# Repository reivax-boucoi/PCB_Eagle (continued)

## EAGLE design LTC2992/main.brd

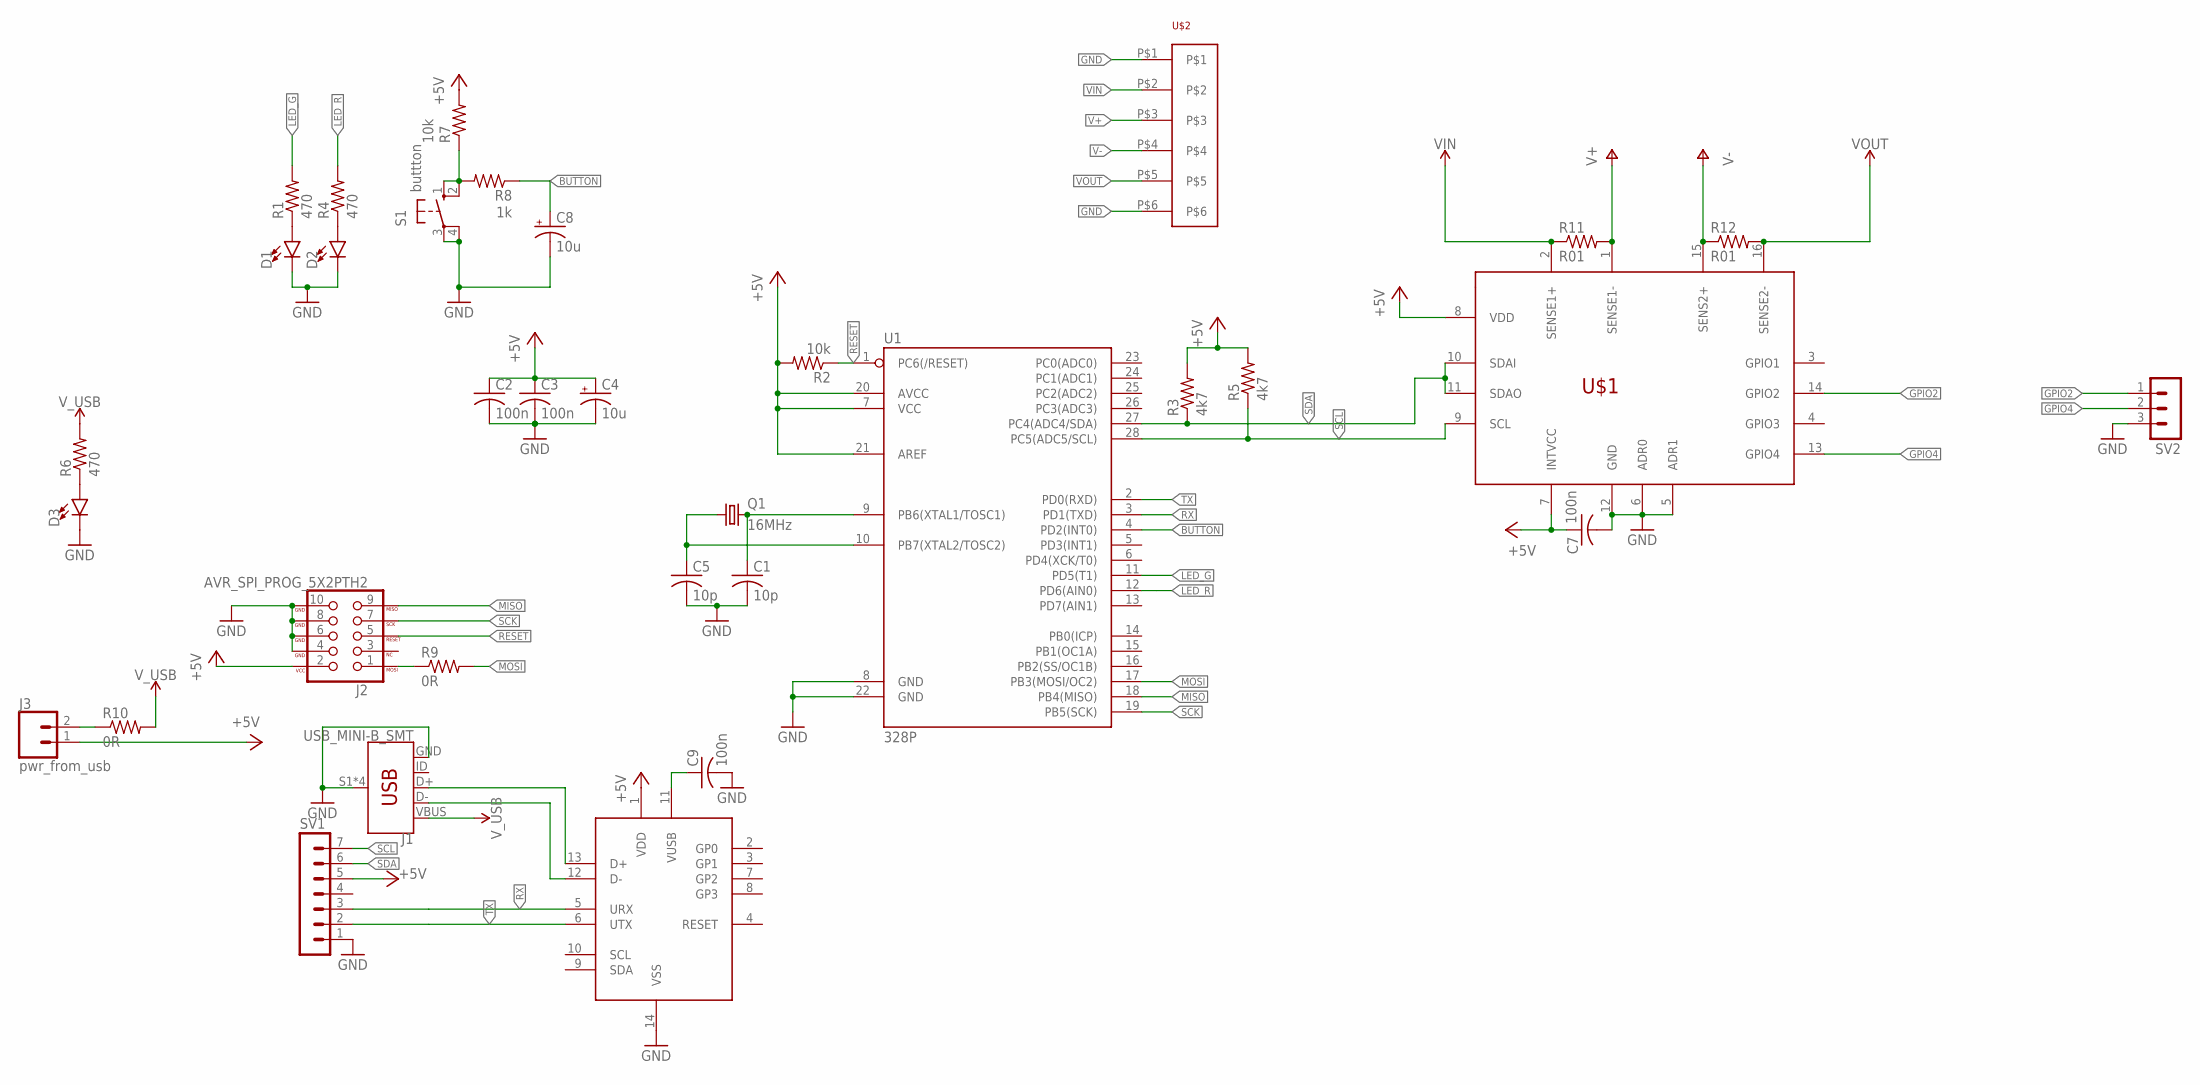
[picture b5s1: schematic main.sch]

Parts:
BR1: MCP2221A; DIP14
C1, C5: 10p; C0603
C2, C9: 100n; C050-030X075
C3, C7: 100n; C0805
C4: 10u; E2,5-6E
C8: 10u; E5-5
D1, D2, D3: LED3MM; LED_3MM
J1: USB_MINI-B_SMT; USB-MINIB
J2: AVR_SPI_PROG_5X2PTH2; 2X5-SHROUDED
J3: pwr_from_usb; 1X02
Q1: 16MHz; HC49U70
R1, R4, R6: 470; R0805
R2: 10k; 0204/7
R3, R5: 4k7; 0207/10
R7: 10k; R0805
R8: 1k; R0805
R9: 0R; 0204/7
R10: 0R; 0207/15
R11, R12: R01; R2512
S1: buttton; B3F-10XX
SV1: MA07-1
SV2: MA03-1
U1: 328P; DIP28
U$1: LTC2992; MSOP16
U$2: SCREWTERM_5MM_6WAY

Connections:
+5V: BR1.1 (VDD), C2.1, C3.1, C4.+, C7.1, J2.2 (VCC), J3.1, R2.2, R3.2, R5.2, R7.2, SV1.5, U1.7 (VCC), U1.20 (AVCC), U1.21 (AREF), U$1.7 (INTVCC), U$1.8 (VDD)
BUTTON: C8.+, R8.1, U1.4 (PD2(INT0))
GND: BR1.14 (VSS), C1.2, C2.2, C3.2, C4.-, C5.2, C7.2, C8.-, C9.2, D1.K (C), D2.K (C), D3.K (C), J1.GND, J1.S1 (SHIELD), J1.S2 (SHIELD), J1.S3 (SHIELD), J1.S4 (SHIELD), J2.4 (GND), J2.6 (GND), J2.8 (GND), J2.10 (GND), S1.3, S1.4 (P1), SV1.1, SV2.3, U1.8 (GND), U1.22 (GND), U$1.5 (ADR1), U$1.6 (ADR0), U$1.12 (GND), U$2.P$1, U$2.P$6
GPIO2: SV2.1, U$1.14 (GPIO2)
GPIO4: SV2.2, U$1.13 (GPIO4)
LED_G: R1.2, U1.11 (PD5(T1))
LED_R: R4.2, U1.12 (PD6(AIN0))
MISO: J2.9 (MISO), U1.18 (PB4(MISO))
MOSI: R9.2, U1.17 (PB3(MOSI/OC2))
unnamed: C1.1, Q1.2, U1.9 (PB6(XTAL1/TOSC1))
unnamed: C5.1, Q1.1, U1.10 (PB7(XTAL2/TOSC2))
unnamed: D3.A, R6.1
unnamed: BR1.13 (D+), J1.D+
unnamed: BR1.12 (D-), J1.D-
unnamed: D2.A, R4.1
unnamed: R7.1, R8.2, S1.1 (S), S1.2 (S1)
unnamed: D1.A, R1.1
unnamed: J2.1 (MOSI), R9.1
unnamed: BR1.11 (VUSB), C9.1
unnamed: J3.2, R10.1
RESET: J2.5 (RESET), R2.1, U1.1 (PC6(/RESET))
RX: BR1.5 (URX), SV1.3, U1.3 (PD1(TXD))
SCK: J2.7 (SCK), U1.19 (PB5(SCK))
SCL: R5.1, SV1.7, U1.28 (PC5(ADC5/SCL)), U$1.9 (SCL)
SDA: R3.1, SV1.6, U1.27 (PC4(ADC4/SDA)), U$1.10 (SDAI), U$1.11 (SDAO)
TX: BR1.6 (UTX), SV1.2, U1.2 (PD0(RXD))
V+: R11.2, U$1.1 (SENSE1-), U$2.P$3
V-: R12.1, U$1.15 (SENS2+), U$2.P$4
VIN: R11.1, U$1.2 (SENSE1+), U$2.P$2
VOUT: R12.2, U$1.16 (SENSE2-), U$2.P$5
V_USB: J1.VBUS, R6.2, R10.2

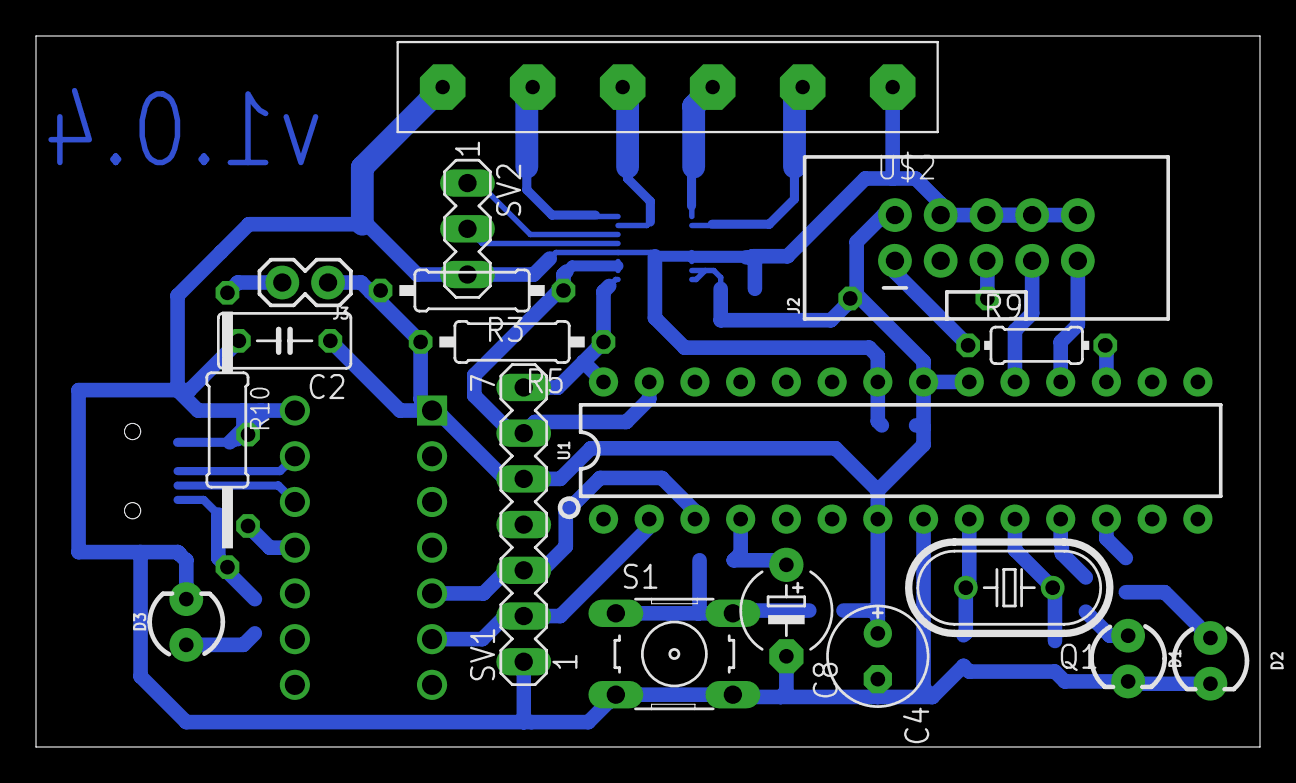
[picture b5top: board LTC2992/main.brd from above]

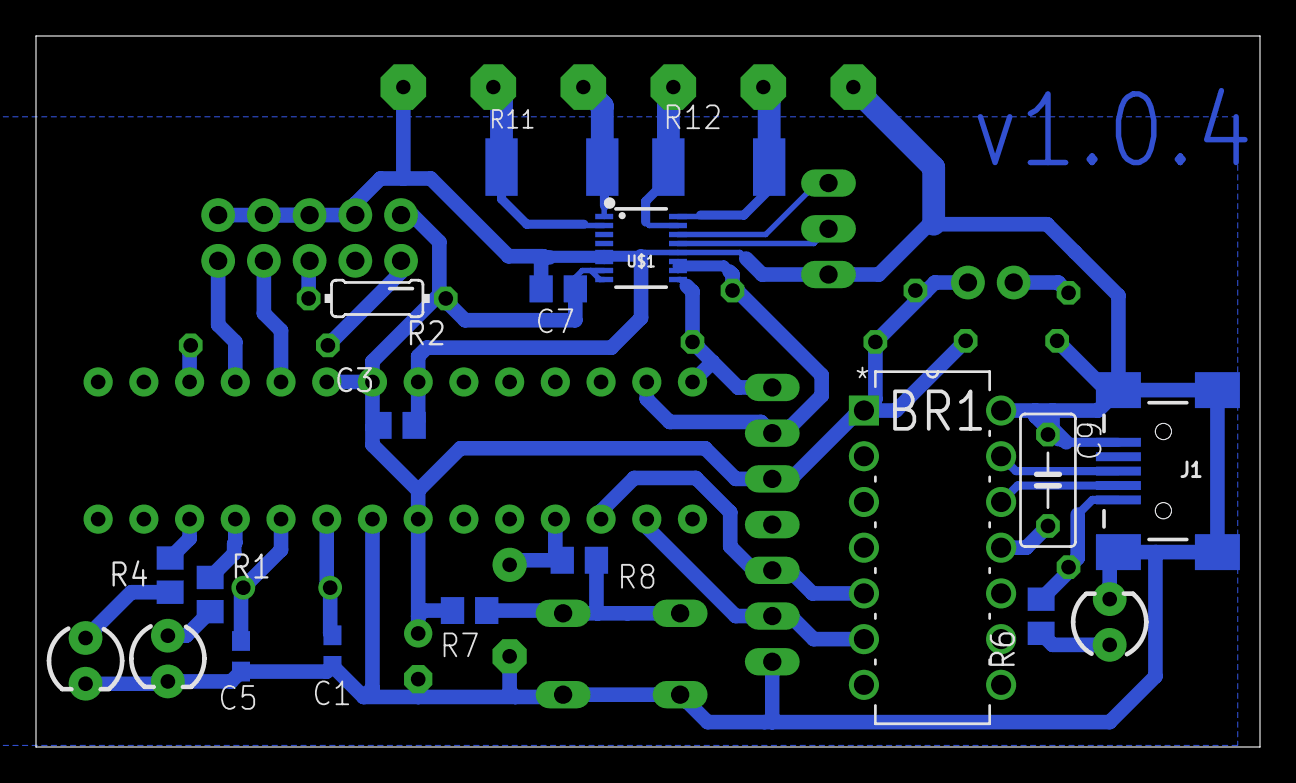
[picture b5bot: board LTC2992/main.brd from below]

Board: 2 copper layers, 68.0 x 39.5 mm, 34 parts (16 on the bottom side), 31 nets.

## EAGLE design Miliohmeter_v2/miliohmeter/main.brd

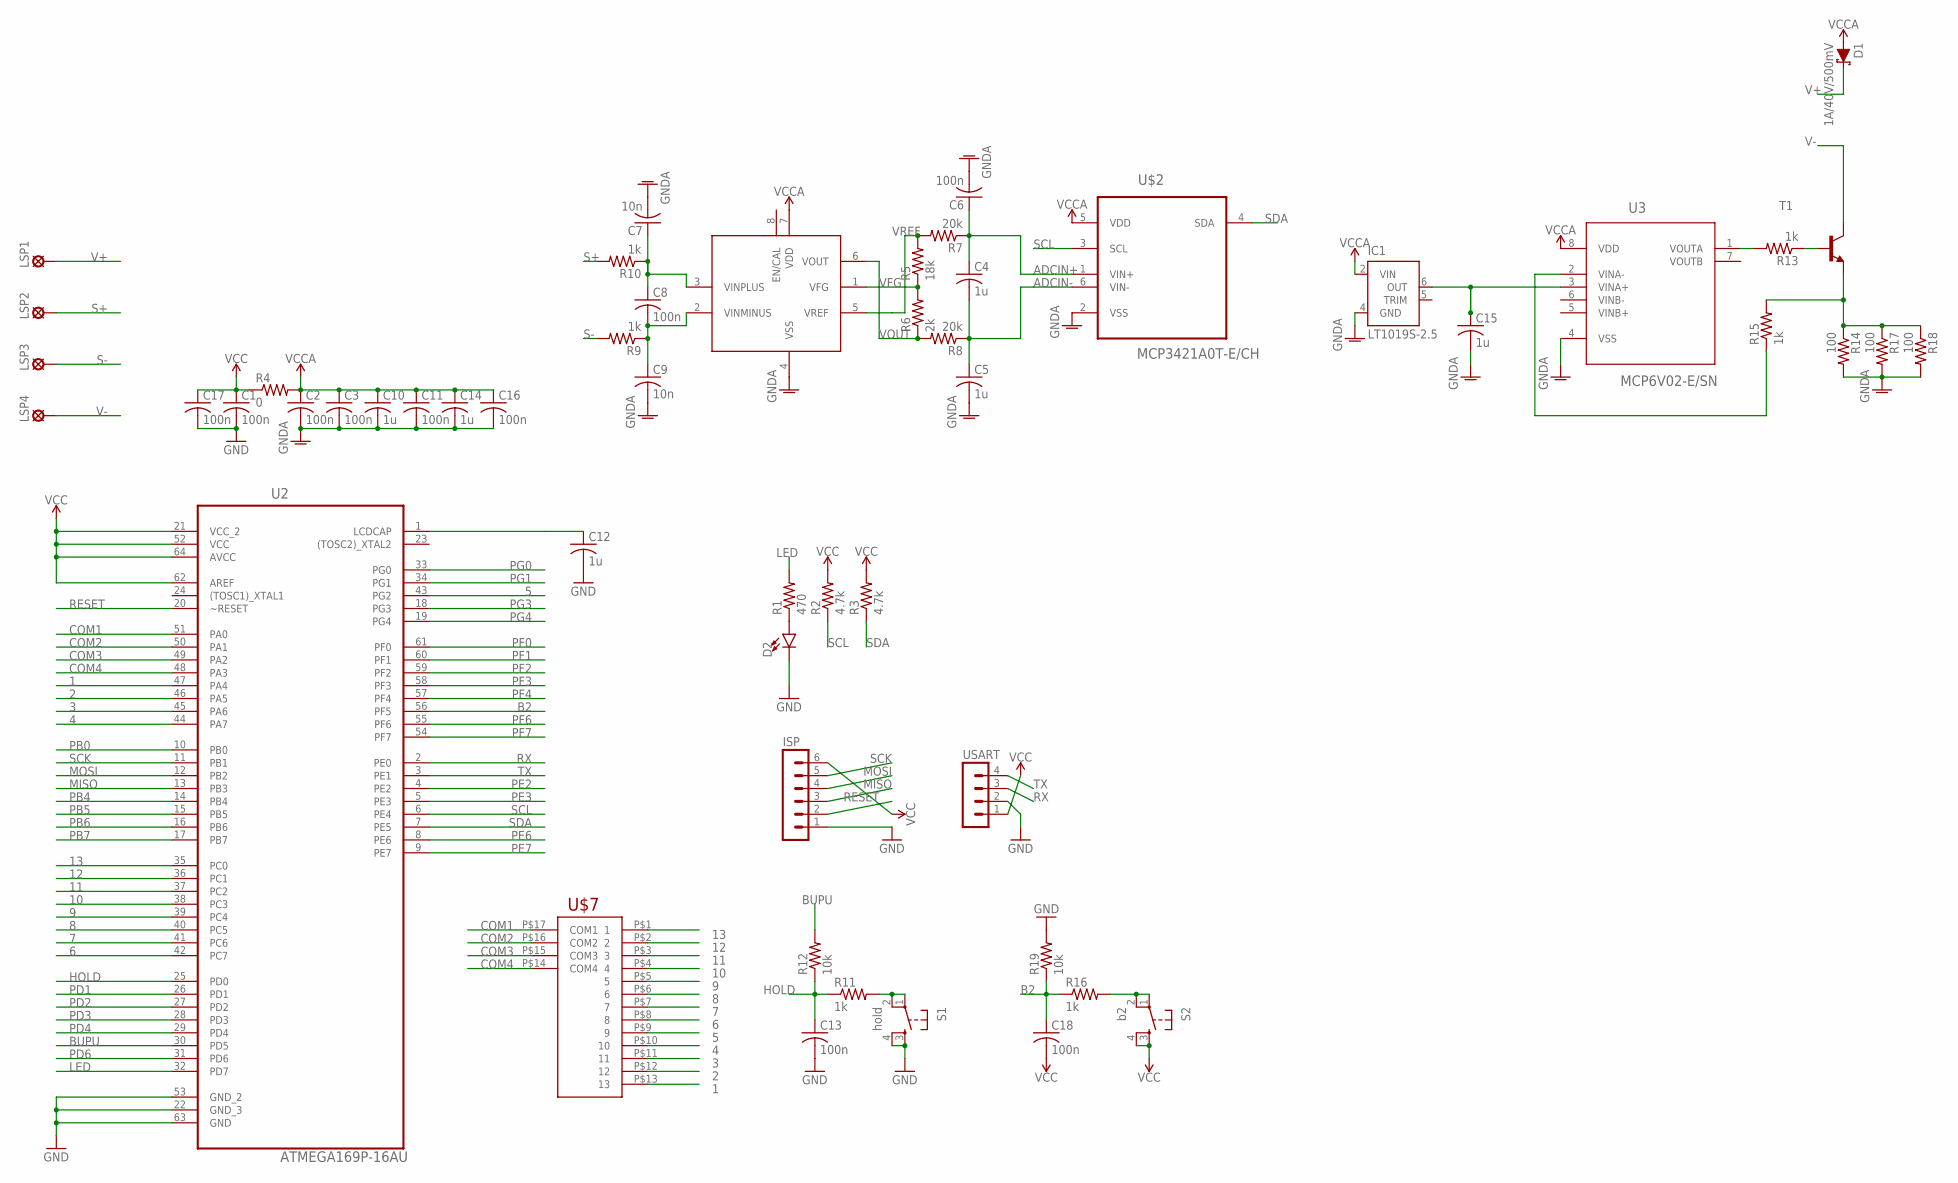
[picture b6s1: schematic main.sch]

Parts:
C1, C2, C3, C6, C8, C11, C13, C16, C17, C18: 100n; C0603
C4, C5, C10, C12, C14, C15: 1u; C0603
C7, C9: 10n; C0603
D1: 1A/40V/500mV; SMA-DIODE
D2: LED5MM; LED_5MM
IC1: LT1019S-2.5; SOIC8
ISP: MA06-1
LSP1, LSP2, LSP3, LSP4: MCS08
R1: 470; R0603
R2, R3: 4.7k; R0603
R4: 0; 0309/12
R5: 18k; R0603
R6: 2k; R0603
R7, R8: 20k; R0603
R9, R10, R11, R13, R15, R16: 1k; R0603
R12, R19: 10k; R0603
R14, R17, R18: 100; R0603
S1: hold; TACTILE-PTH
S2: b2; TACTILE-PTH
T1: MMBT3904LT1-NPN-SOT23-BEC; SOT23-BEC
U2: ATMEGA169P-16AU; QFP80P1600X1600X120-64N
U3: MCP6V02-E/SN; SOIC127P600X175-8N
U$2: MCP3421A0T-E/CH; SOT95P270X145-6N
U$3: MCP6N11; SOIC8
U$7: GDC0570_LCD
USART: MA04-1

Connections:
1: U2.47 (PA4), U$7.P$13 (13)
2: U2.46 (PA5), U$7.P$12 (12)
3: U2.45 (PA6), U$7.P$11 (11)
4: U2.44 (PA7), U$7.P$10 (10)
5: U2.43 (PG2), U$7.P$9 (9)
6: U2.42 (PC7), U$7.P$8 (8)
7: U2.41 (PC6), U$7.P$7 (7)
8: U2.40 (PC5), U$7.P$6 (6)
9: U2.39 (PC4), U$7.P$5 (5)
10: U2.38 (PC3), U$7.P$4 (4)
11: U2.37 (PC2), U$7.P$3 (3)
12: U2.36 (PC1), U$7.P$2 (2)
13: U2.35 (PC0), U$7.P$1 (1)
ADCIN+: C4.1, C6.1, R7.1, U$2.1 (VIN+)
ADCIN-: C4.2, C5.1, R8.1, U$2.6 (VIN-)
B2: C18.1, R16.1, R19.1, U2.56 (PF5)
BUPU: R12.2, U2.30 (PD5)
COM1: U2.51 (PA0), U$7.P$17 (COM1)
COM2: U2.50 (PA1), U$7.P$16 (COM2)
COM3: U2.49 (PA2), U$7.P$15 (COM3)
COM4: U2.48 (PA3), U$7.P$14 (COM4)
GND: C1.2, C12.2, C13.2, C17.2, D2.K (C), ISP.1, R19.2, S1.3, S1.4, U2.22 (GND_3), U2.53 (GND_2), U2.63 (GND), USART.2
GNDA: C2.2, C3.2, C5.2, C6.2, C7.2, C9.2, C10.2, C11.2, C14.2, C15.2, C16.2, IC1.4 (GND), R14.2, R17.2, R18.2, U3.4 (VSS), U$2.2 (VSS), U$3.4 (VSS)
HOLD: C13.1, R11.1, R12.1, U2.25 (PD0)
LCDCAP: C12.1, U2.1 (LCDCAP)
LED: R1.2, U2.32 (PD7)
MISO: ISP.3, U2.13 (PB3)
MOSI: ISP.4, U2.12 (PB2)
N2: R16.2, S2.1, S2.2
unnamed: C15.1, IC1.6 (OUT), U3.3 (VINA+)
unnamed: R14.1, R15.2, R17.1, R18.1, T1.E
unnamed: C8.2, C9.1, R9.1, U$3.2 (VINMINUS)
unnamed: C7.1, C8.1, R10.1, U$3.3 (VINPLUS)
unnamed: D2.A, R1.1
unnamed: R13.2, U3.1 (VOUTA)
unnamed: R13.1, T1.B
unnamed: R15.1, U3.2 (VINA-)
unnamed: R11.2, S1.1, S1.2
PB0: U2.10 (PB0)
PB4: U2.14 (PB4)
PB5: U2.15 (PB5)
PB6: U2.16 (PB6)
PB7: U2.17 (PB7)
PD1: U2.26 (PD1)
PD2: U2.27 (PD2)
PD3: U2.28 (PD3)
PD4: U2.29 (PD4)
PD6: U2.31 (PD6)
PE2: U2.4 (PE2)
PE3: U2.5 (PE3)
PE6: U2.8 (PE6)
PE7: U2.9 (PE7)
PF0: U2.61 (PF0)
PF1: U2.60 (PF1)
PF2: U2.59 (PF2)
PF3: U2.58 (PF3)
PF4: U2.57 (PF4)
PF6: U2.55 (PF6)
PF7: U2.54 (PF7)
PG0: U2.33 (PG0)
PG1: U2.34 (PG1)
PG3: U2.18 (PG3)
PG4: U2.19 (PG4)
RESET: ISP.2, U2.20 (~RESET)
RX: U2.2 (PE0), USART.3
S+: LSP2.MP, R10.2
S-: LSP3.MP, R9.2
SCK: ISP.5, U2.11 (PB1)
SCL: R2.1, U2.6 (PE4), U$2.3 (SCL)
SDA: R3.1, U2.7 (PE5), U$2.4 (SDA)
TX: U2.3 (PE1), USART.4
V+: D1.C, LSP1.MP
V-: LSP4.MP, T1.C
VCC: C1.1, C17.1, C18.2, ISP.6, R2.2, R3.2, R4.1, S2.3, S2.4, U2.21 (VCC_2), U2.52 (VCC), U2.62 (AREF), U2.64 (AVCC), USART.1
VCCA: C2.1, C3.1, C10.1, C11.1, C14.1, C16.1, D1.A, IC1.2 (VIN), R4.2, U3.8 (VDD), U$2.5 (VDD), U$3.7 (VDD)
VFG: R5.1, R6.2, U$3.1 (VFG)
VOUT: R6.1, R8.2, U$3.6 (VOUT)
VREF: R5.2, R7.2, U$3.5 (VREF)

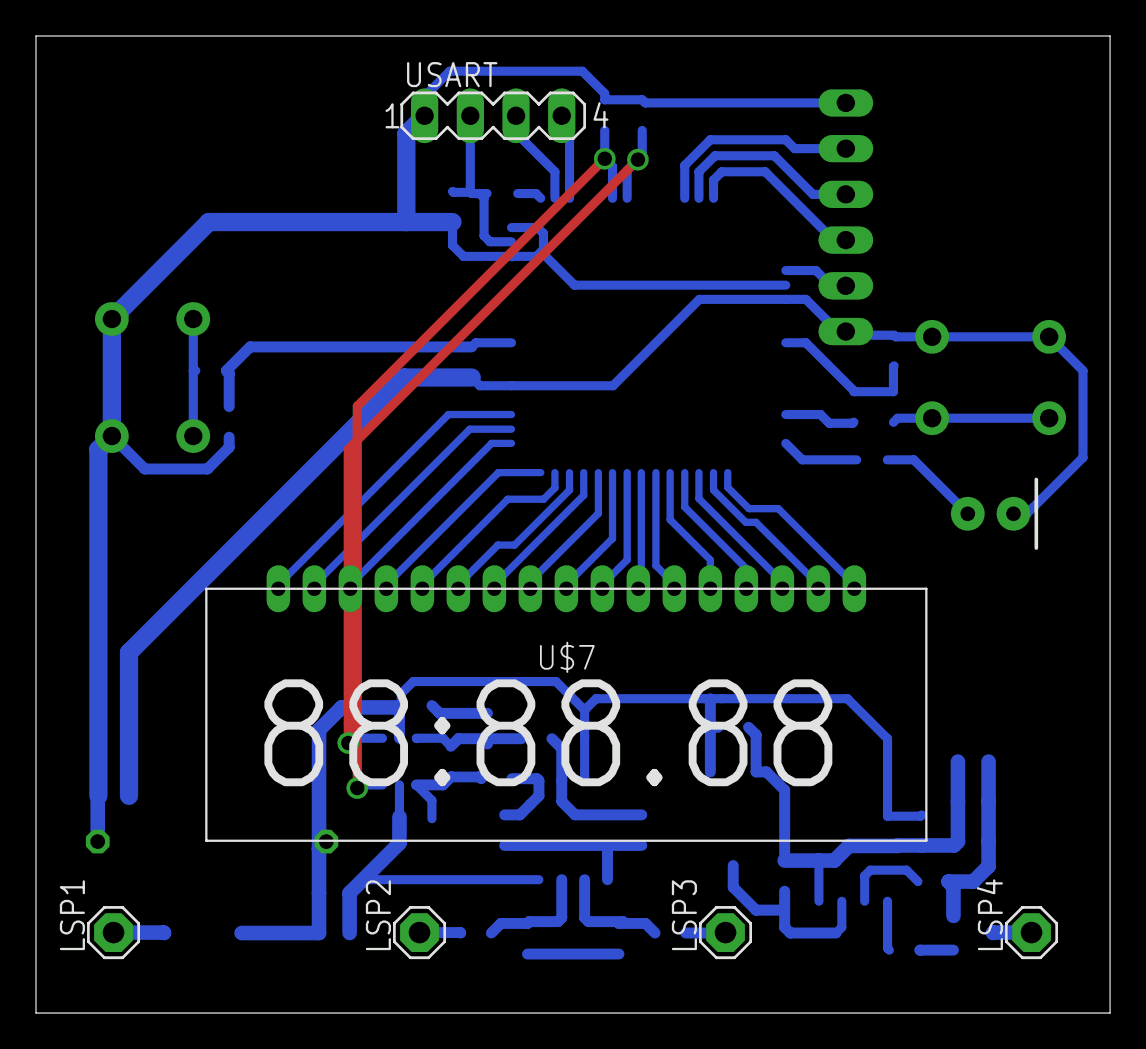
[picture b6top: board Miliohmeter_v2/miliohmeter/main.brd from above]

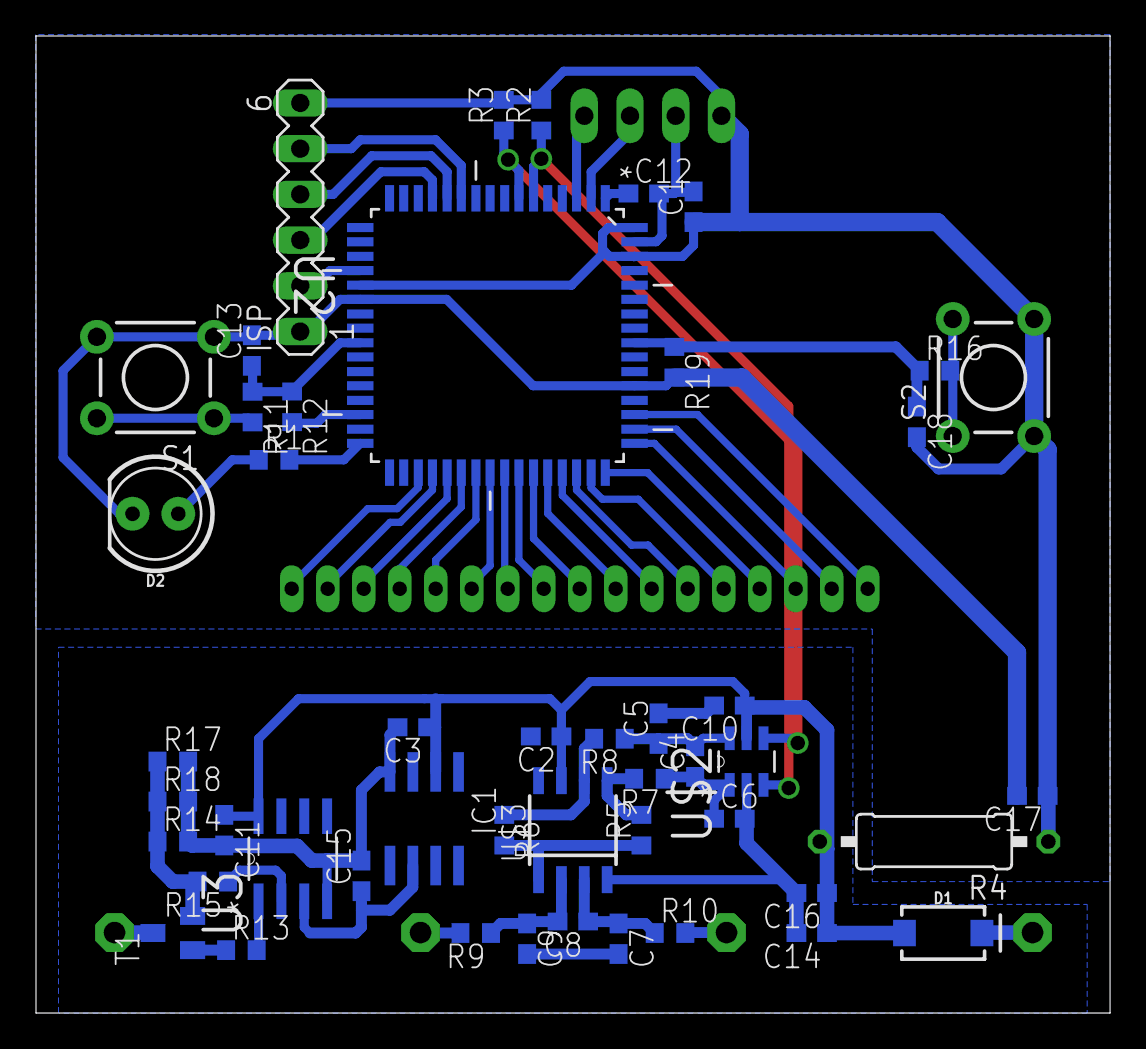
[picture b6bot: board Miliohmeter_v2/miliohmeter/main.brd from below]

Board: 2 copper layers, 59.7 x 54.3 mm, 54 parts (48 on the bottom side), 53 nets.

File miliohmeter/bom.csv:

Qty;Value;Device;Parts
1;;LED5MM;D2
1;;MA04-1;USART
1;;MMBT3904LT1-NPN-SOT23-BEC;T1
1;;PINHD-1X2;PWR
1;;PINHD-1X6;ISP
1;0;R-US_0309/12;R4
1;0;R-US_R0603;R21
4;100;R-US_R0603;R14, R17, R18, R20
12;100n;C-USC0603;C1, C2, C3, C6, C8, C11, C13, C16, C17, C18, C19, C20
2;10k;R-US_R0603;R12, R19
2;10n;C-USC0603;C7, C9
1;18k;R-US_R0603;R5
2;1A/40V/500mV;DIODE-SCHOTTKY-SS14;D1, D3
6;1k;R-US_R0603;R9, R10, R11, R13, R15, R16
6;1u;C-USC0603;C4, C5, C10, C12, C14, C15
2;20k;R-US_R0603;R7, R8
1;2k;R-US_R0603;R6
2;4.7k;R-US_R0603;R2, R3
1;470;R-US_R0603;R1
1;7805TV;7805TV;REG1
1;ATMEGA169P-16AU;ATMEGA169P-16AU;U2
1;GDC0570_LCD;GDC0570_LCD;LCD1
1;LT1019S-2.5;LT1019S-2.5;IC1
1;MCP3421A0T-E/CH;MCP3421A0T-E/CH;U$2
1;MCP6N11;MCP6N11;U$3
1;MCP6V02-E/SN;MCP6V02-E/SN;U3
4;MCS08;MCS08;S+, S-, V+, V-
1;SHORT32;SHORT32;U$10
1;b2;TAC_SWITCHPTH;S2
1;hold;TAC_SWITCHPTH;S1

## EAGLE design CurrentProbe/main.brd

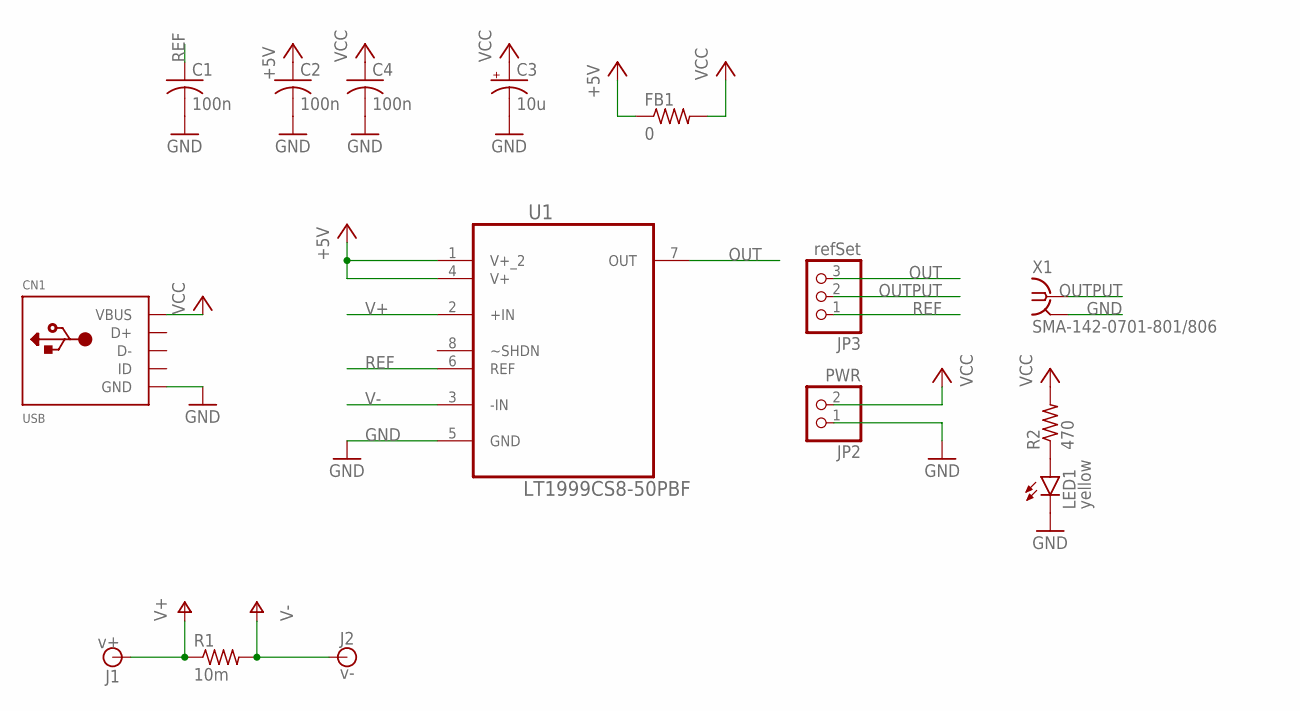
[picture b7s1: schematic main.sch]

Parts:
C1, C2, C4: 100n; C0805
C3: 10u; E2-5
CN1: USB; USB-MINIB
FB1: 0; 0204/7
J1: v+; BANANA_CONN
J2: v-; BANANA_CONN
JP2: PWR; 1X02
JP3: refSet; 1X03
LED1: yellow; CHIP-LED0603
R1: 10m; R2512
R2: 470; R0603
U1: LT1999CS8-50PBF; SOIC127P600X175-8N
X1: SMA-142-0701-801/806; J502-ND-142-0701-801/806

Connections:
+5V: C2.1, FB1.1, U1.1 (V+_2), U1.4 (V+)
GND: C1.2, C2.2, C3.-, C4.2, CN1.GND, JP2.1, LED1.C, U1.5 (GND), X1.G@1 (2), X1.G@2 (2), X1.G@3 (2), X1.G@4 (2)
unnamed: LED1.A, R2.1
OUT: JP3.3, U1.7 (OUT)
OUTPUT: JP3.2, X1.1
REF: C1.1, JP3.1, U1.6 (REF)
V+: J1.P$1, R1.1, U1.2 (+IN)
V-: J2.P$1, R1.2, U1.3 (-IN)
VCC: C3.+, C4.1, CN1.VBUS, FB1.2, JP2.2, R2.2

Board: 2 copper layers, 15 parts (0 on the bottom side), 9 nets, no tracks yet.

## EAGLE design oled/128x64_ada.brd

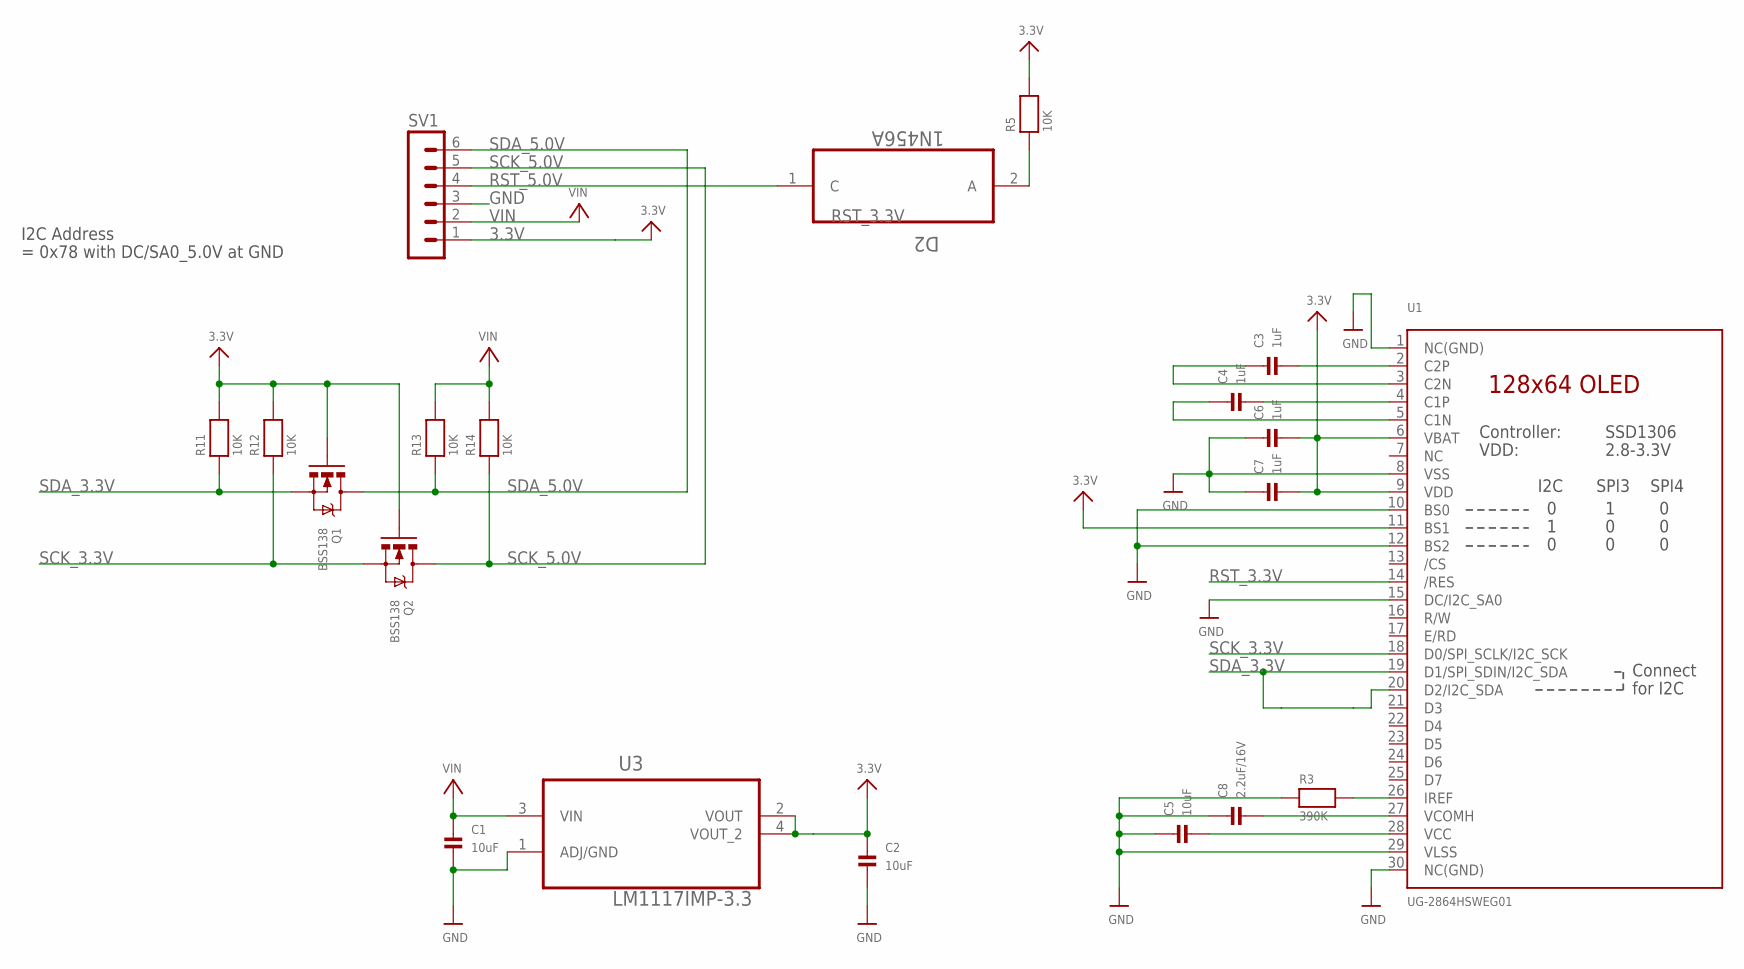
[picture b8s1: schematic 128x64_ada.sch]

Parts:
C1, C2, C5: 10uF; 0805
C3, C4, C6, C7: 1uF; 0805
C8: 2.2uF/16V; 0805
D2: 1N456A; DIO_1N456A
Q1, Q2: BSS138; SOT323
R3: 390K; 0805
R5, R11, R12, R13, R14: 10K; 0603
SV1: MA06-1
U1: UG-2864HSWEG01; UG-2864HSWEG01_0.96IN_WRAPAROUND
U3: LM1117IMP-3.3; SOT230P696X180-4N

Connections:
3.3V: C2.1, C6.2, C7.2, Q1.1 (G), Q2.1 (G), R5.2, R11.2, R12.2, SV1.1, U1.6 (VBAT), U1.9 (VDD), U1.11 (BS1), U3.2 (VOUT), U3.4 (VOUT_2)
GND: C1.2, C2.2, C5.1, C6.1, C7.1, C8.1, R3.1, SV1.3, U1.1 (NC(GND)), U1.8 (VSS), U1.10 (BS0), U1.12 (BS2), U1.15 (DC/I2C_SA0), U1.29 (VLSS), U1.30 (NC(GND)), U3.1 (ADJ/GND)
unnamed: R3.2, U1.26 (IREF)
unnamed: C3.2, U1.2 (C2P)
unnamed: C3.1, U1.3 (C2N)
unnamed: C4.2, U1.4 (C1P)
unnamed: C4.1, U1.5 (C1N)
unnamed: C5.2, U1.28 (VCC)
unnamed: C8.2, U1.27 (VCOMH)
RST_3.3V: D2.2 (A), R5.1, U1.14 (/RES)
RST_5.0V: D2.1 (C), SV1.4
SCK_3.3V: Q2.2 (S), R12.1, U1.18 (D0/SPI_SCLK/I2C_SCK)
SCK_5.0V: Q2.3 (D), R14.1, SV1.5
SDA_3.3V: Q1.2 (S), R11.1, U1.19 (D1/SPI_SDIN/I2C_SDA), U1.20 (D2/I2C_SDA)
SDA_5.0V: Q1.3 (D), R13.1, SV1.6
VIN: C1.1, R13.2, R14.2, SV1.2, U3.3 (VIN)

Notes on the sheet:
= 0x78 with DC/SA0_5.0V at GND
I2C Address

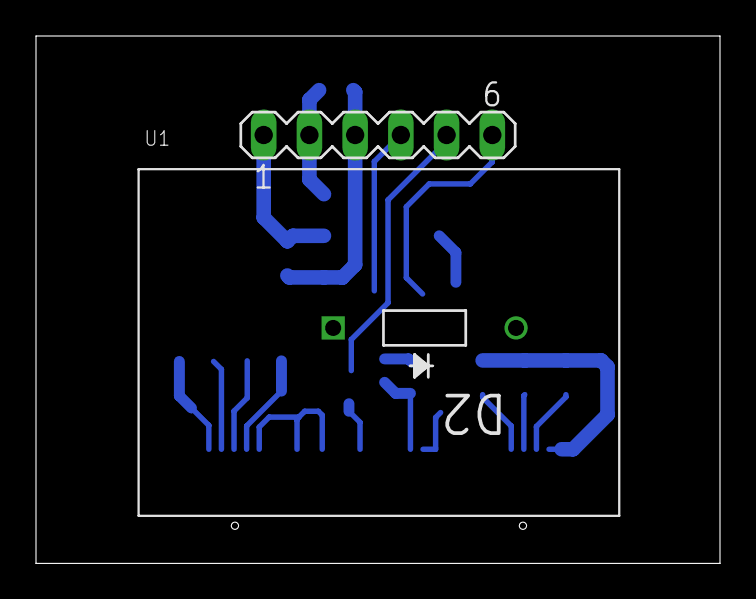
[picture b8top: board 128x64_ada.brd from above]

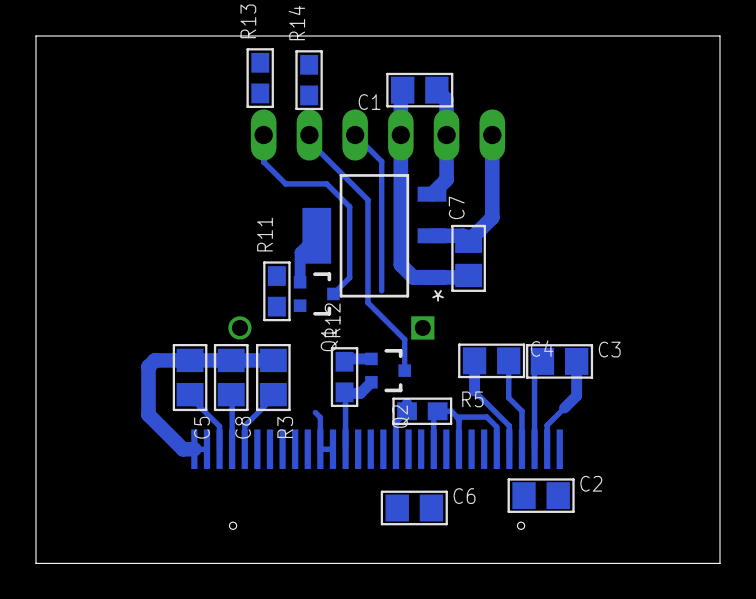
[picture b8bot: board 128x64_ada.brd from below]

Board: 2 copper layers, 38.0 x 29.3 mm, 20 parts (17 on the bottom side), 16 nets.

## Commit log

2017-12-15 updated project
2018-03-03 usb pro
2018-03-04 Create LICENSE
2018-04-30 sdfsdfsff
2018-05-17 kjhkjh
2018-05-19 sdsfd
2018-05-19 dded pdf
2018-05-21 jhglkjh
2018-05-31 aeazeaze
2018-05-31 lhjgjh
2018-06-07 kjhkj
2018-06-23 miliohmeter
2018-06-24 azeaze
2018-06-27 miliohmmeter
2018-06-27 aeaz
2018-07-01 lkjlk
2018-07-09 updated .gitignore
2018-07-11 added gitignore
2018-07-11 customized .gitignore
2018-07-11 git rm --cached
2018-07-12 started power logger
2018-07-12 added lcmeter
2018-10-17 fablab update
2018-11-10 wordclock
2018-12-16 added MCP2210
2018-12-19 added usb conn
2018-12-20 added board
2019-01-02 resized outline
2019-01-03 added crystal
2019-01-05 added 2nd layout
2019-01-08 started new layout
2019-01-13 -a
    a
2019-02-03 -a
    a*
2019-02-04 added a
2019-05-11 added offline led drivers
2020-10-26 updated eagle epf
